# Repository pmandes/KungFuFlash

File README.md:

# Kung Fu Flash - Long PCB version

This version of the cartridge was developed for the following purposes:
- to fit into standard housings matching PCBs in format and size of the EasyFlash 3 cartridge
- to make SMD manual soldering easier
- to prevent the leverage effect when pressing the buttons from above, which stressed the cartridge connector and caused the C64 to crash.

The original design can be found [here](https://github.com/KimJorgensen/KungFuFlash).

Main changes:
- project migrated to KiCad 6.0
- 3D models for all components
- long PCB to fit common housings
- right angle tactile switches
- more durable Mini USB B socket for data transfer (you can use the same cable as EF3)
- 100Ω 0805 resistors for easier manual soldering (instead of resitor arrays)

The gerber files:
[KungFuFlash-Long-v2.1-PM.zip](https://github.com/pmandes/KungFuFlash/blob/long-board-cart/hardware/gerber/KungFuFlash-Long-v2.1-PM.zip)

Compatible housings:
- [KM-20B](https://www.tme.eu/en/details/km-20b/multipurpose-enclosures/maszczyk/)
- [Z7](https://www.kradex.eu/product/enclosures_two_part/z7_ps?lang=en)
- [Thingiverse](https://www.thingiverse.com/thing:1702546)
- "Commodore" type and others that EF3 fits

# Kung Fu Flash
Cartridge for the Commodore 64 that packs a punch.

Kung Fu Flash can emulate different cartridge types, load PRG files and use D64 disk images.
Just place your desired CRT, PRG or D64 files on a FAT formatted microSD card and use the built-in launcher to execute them.

## Hardware
There are three buttons on the cartridge; a reset button, a menu button for starting the launcher, and a special button that is used by the freezer cartridges.

The PCB will fit the Stumpy Cartridge Case from TFW8b, you just need to drill some holes for the buttons and make a cut for the microSD card.
If you have mounted the USB connector you will need to cut a hole for that as well.

You can also 3D print a cartridge case as the one designed by bigby, [see here](https://www.thingiverse.com/thing:4153414).

The gerber files and BOM can be found [here](https://github.com/KimJorgensen/KungFuFlash/releases/tag/rev.2).

## Supported Cartridges
The following cartridge types are currently supported:

* Normal cartridge (8k, 16k, Ultimax)
* Action Replay v4.x/v5/v6
* KCS Power Cartridge
* Final Cartridge III(+)
* Simons' BASIC
* Fun Play, Power Play
* Super Games
* Ocean type 1
* Epyx Fastload
* C64 Game System, System 3
* WarpSpeed
* Dinamic
* Zaxxon, Super Zaxxon
* Magic Desk, Domark, HES Australia
* Super Snapshot v5
* Comal-80
* EasyFlash
* Prophet64
* Freeze Frame
* Freeze Machine
* RGCD, Hucky
* Drean
* C128 Normal Cartridge (external function ROM)

## Supported File Types
The following file types are currently supported:

* Cartridge (CRT)
* C128 cartridge (ROM, BIN)
* Disk image (D64, D71, D81)
* Tape image (T64)
* Program (PRG, P00)
* Firmware update (UPD)

## USB Port
The USB port is active while the launcher is running allowing programs to be transferred from a PC using the EasyFlash 3 USB protocol.
Kung Fu Flash shows up as a standard serial port when connected to a PC not requiring any custom drivers to be installed.
This means, however, that the program on the PC side must be modified to support Kung Fu Flash.
For that reason a modified version of [EasyFlash 3 USB Utilities](3rd_party/ef3utils) and [EasyFlash 3 BBS](3rd_party/ef3bbs) has been included in this repository.

## Firmware Update
Just place the KungFuFlash_v1.xx.upd file on the SD card and select the file in the launcher to initiate the firmware update.
The newest firmware can be found [here](https://github.com/KimJorgensen/KungFuFlash/releases/).

For initial firmware installation, [see here](firmware/README.md).

## Limitations
Kung Fu Flash is a so called Software Defined Cartridge where a fast microcontroller emulates cartridge hardware in software.
This makes it extremely flexible, allowing different cartridge types to be supported at a relative low cost.

However, it can be challenging to get the C64 bus timing correct in software and in some places the timing is very close to the limit.
Even though Kung Fu Flash has been tested on different models of the Commodore 64, there is a chance that it doesn't work correctly on your specific model.
Use it at your own risk!

Kung Fu Flash will work with the PAL version of the Commodore 64 or Commodore 128. Support for the NTSC version is still considered experimental.

Disk drive emulation is using kernal vectors and will not work with fast loaders or software that uses direct hardware access which a lot of games does. Currently REL files are not supported and there is only limited write support.

## Thanks
Kung Fu Flash was based on or uses other open source projects:

* [EasyFlash 3](https://bitbucket.org/skoe/easyflash) by Thomas Giesel
* [Draco Browser](https://csdb.dk/release/?id=89910) by Sascha Bader
* [fatfs-stm32](https://github.com/colosimo/fatfs-stm32) by Aurelio Colosimo
* [FatFs](http://elm-chan.org/fsw/ff/00index_e.html) by ChaN
* [libusb_stm32](https://github.com/dmitrystu/libusb_stm32) by Dmitry Filimonchuk
* [stm32f4-bare-metal](https://github.com/fcayci/stm32f4-bare-metal) by Furkan Cayci
* [OpenC64Cart](https://github.com/SukkoPera/OpenC64Cart) by Giorgioggì
* [EasyFlash 3 USB Utilities](https://csdb.dk/release/?id=150097) by Tomaz Kac
* [Disk2easyflash](https://csdb.dk/release/?id=150323) by ALeX Kazik

and a few others. Please check the individual files for their license.

Thanks to Bjørn N. Jørgensen for giving this project its name.

Special thanks to the author of [Sidekick64](https://github.com/frntc/Sidekick64) Carsten Dachsbacher for his support and inspiration.

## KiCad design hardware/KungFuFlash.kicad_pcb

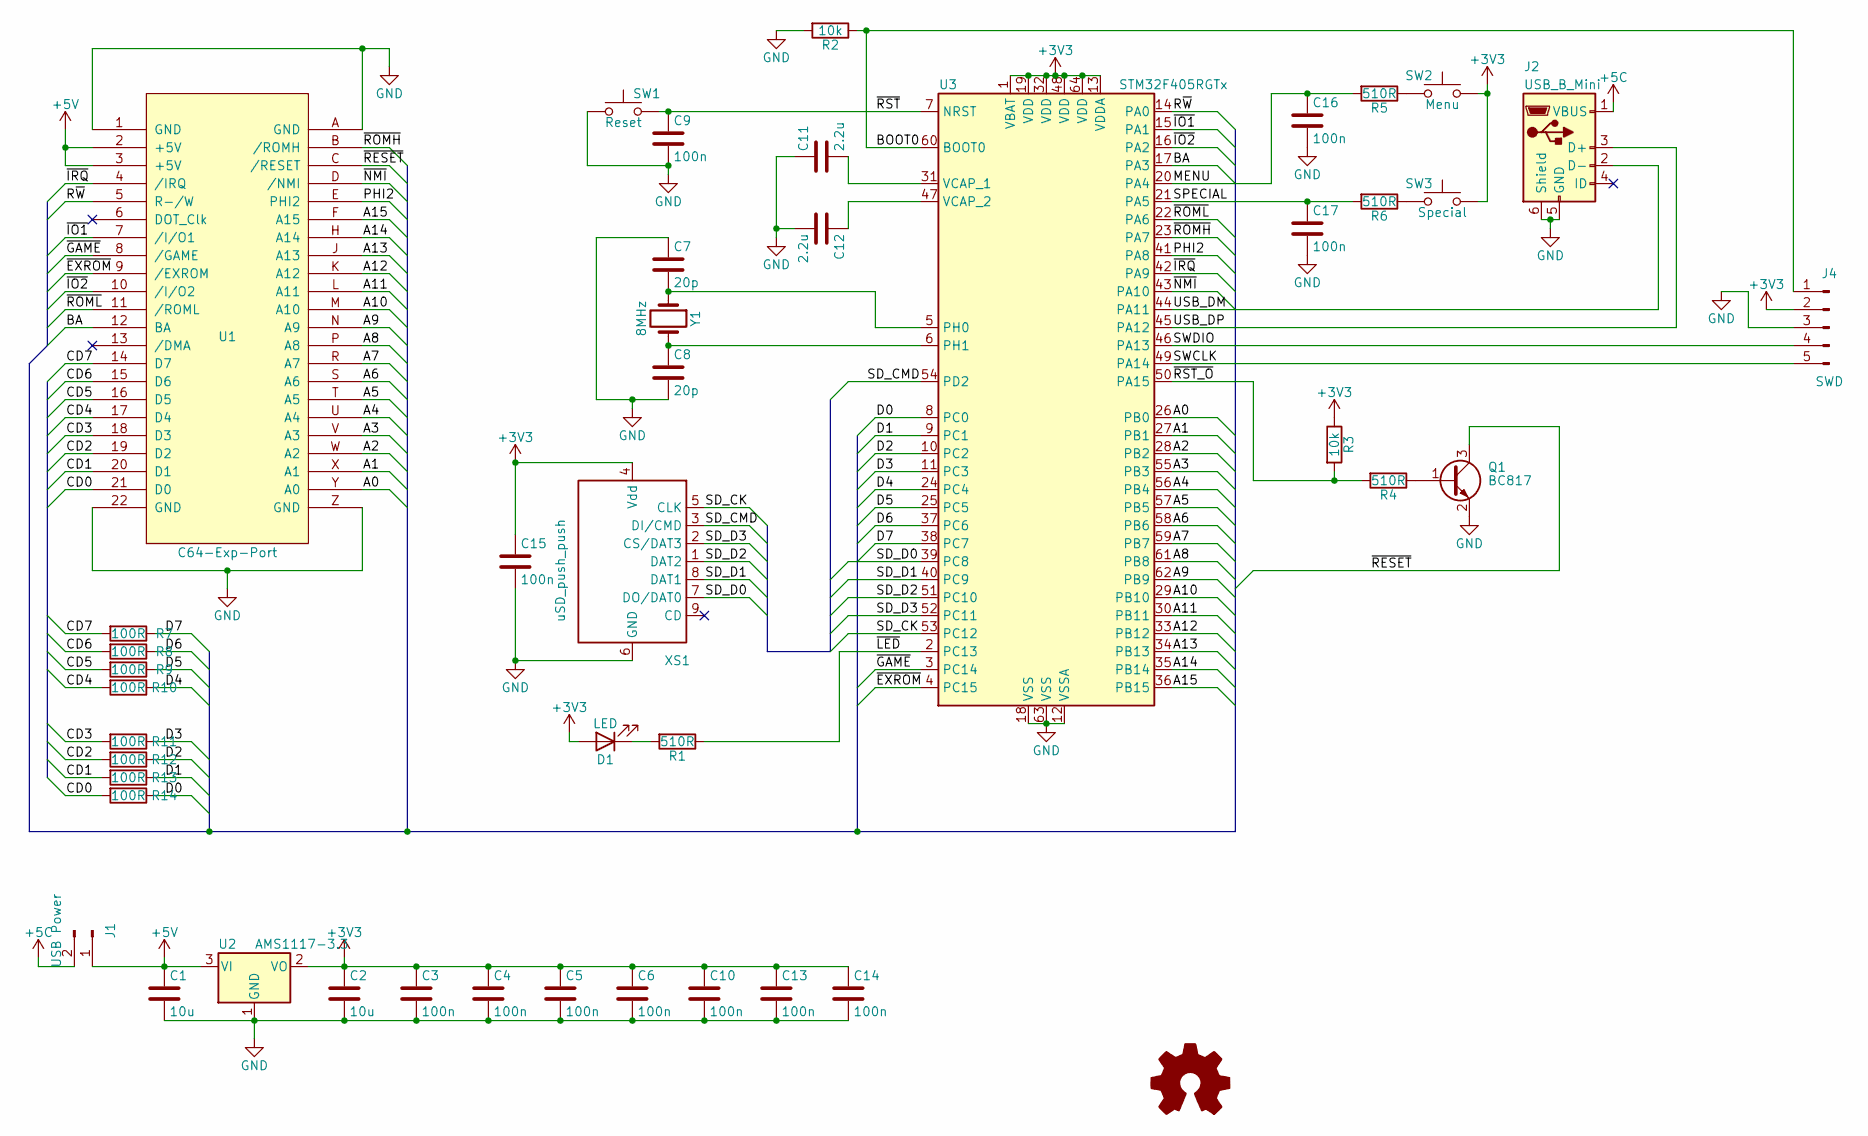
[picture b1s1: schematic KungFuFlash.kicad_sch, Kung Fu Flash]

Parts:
C1, C2: 10u; C_0805_2012Metric_Pad1.18x1.45mm_HandSolder
C3, C4, C5, C6, C9, C10, C13, C14, C15, C16: 100n; C_0603_1608Metric_Pad1.08x0.95mm_HandSolder
C7, C8: 20p; C_0603_1608Metric_Pad1.08x0.95mm_HandSolder
C11, C12: 2.2u; C_0805_2012Metric_Pad1.18x1.45mm_HandSolder
C17: 100n; C_0805_2012Metric_Pad1.18x1.45mm_HandSolder
D1: LED; LED_0805_2012Metric_Pad1.15x1.40mm_HandSolder
J1: USB Power; PinHeader_1x02_P2.54mm_Vertical
J2: USB_B_Mini; USB_Mini-B_Wuerth_65100516121_Horizontal
J4: SWD; PinHeader_1x05_P2.54mm_Vertical
Q1: BC817; SOT-23
R1, R4, R5, R6: 510R; R_0805_2012Metric_Pad1.20x1.40mm_HandSolder
R2, R3: 10k; R_0805_2012Metric_Pad1.20x1.40mm_HandSolder
R7, R8, R9, R10, R11, R12, R13, R14: 100R; R_0805_2012Metric_Pad1.20x1.40mm_HandSolder
SW1: Reset; SW_Tactile_SPST_Angled_PTS645Vx83-2LFS
SW2: Menu; SW_Tactile_SPST_Angled_PTS645Vx83-2LFS
SW3: Special; SW_Tactile_SPST_Angled_PTS645Vx83-2LFS
U1: C64-Exp-Port; C64-Cart
U2: AMS1117-3.3; SOT-223-3_TabPin2
U3: STM32F405RGTx; LQFP-64_10x10mm_P0.5mm
XS1: uSD_push_push; Conn_uSDcard
Y1: 8MHz; Crystal_SMD_5032-2Pin_5.0x3.2mm

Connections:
+3V3: C2.1, C3.1, C4.1, C5.1, C6.1, C10.1, C13.1, C14.1, C15.1, D1.2 (A), J4.2, R3.1, SW2.1, SW3.1, U2.2 (VO), U3.1 (VBAT), U3.13 (VDDA), U3.19 (VDD), U3.32 (VDD), U3.48 (VDD), U3.64 (VDD), XS1.4 (Vdd)
+5C: J1.2, J2.1 (VBUS)
+5V: C1.1, J1.1, U1.2 (+5V), U1.3 (+5V), U2.3 (VI)
/A0: U1.Y (A0), U3.26 (PB0)
/A1: U1.X (A1), U3.27 (PB1)
/A2: U1.W (A2), U3.28 (PB2)
/A3: U1.V (A3), U3.55 (PB3)
/A4: U1.U (A4), U3.56 (PB4)
/A5: U1.T (A5), U3.57 (PB5)
/A6: U1.S (A6), U3.58 (PB6)
/A7: U1.R (A7), U3.59 (PB7)
/A8: U1.P (A8), U3.61 (PB8)
/A9: U1.N (A9), U3.62 (PB9)
/A10: U1.M (A10), U3.29 (PB10)
/A11: U1.L (A11), U3.30 (PB11)
/A12: U1.K (A12), U3.33 (PB12)
/A13: U1.J (A13), U3.34 (PB13)
/A14: U1.H (A14), U3.35 (PB14)
/A15: U1.F (A15), U3.36 (PB15)
/BA: U1.12 (BA), U3.17 (PA3)
/BOOT0: J4.1, R2.1, U3.60 (BOOT0)
/CD0: R14.2, U1.21 (D0)
/CD1: R13.2, U1.20 (D1)
/CD2: R12.2, U1.19 (D2)
/CD3: R11.2, U1.18 (D3)
/CD4: R10.2, U1.17 (D4)
/CD5: R9.2, U1.16 (D5)
/CD6: R8.2, U1.15 (D6)
/CD7: R7.2, U1.14 (D7)
/D0: R14.1, U3.8 (PC0)
/D1: R13.1, U3.9 (PC1)
/D2: R12.1, U3.10 (PC2)
/D3: R11.1, U3.11 (PC3)
/D4: R10.1, U3.24 (PC4)
/D5: R9.1, U3.25 (PC5)
/D6: R8.1, U3.37 (PC6)
/D7: R7.1, U3.38 (PC7)
/MENU: C16.1, R5.2, U3.20 (PA4)
/PHI2: U1.E (PHI2), U3.41 (PA8)
/R~W: U1.5 (R-/W), U3.14 (PA0)
/SD_CK: U3.53 (PC12), XS1.5 (CLK)
/SD_CMD: U3.54 (PD2), XS1.3 (DI/CMD)
/SD_D0: U3.39 (PC8), XS1.7 (DO/DAT0)
/SD_D1: U3.40 (PC9), XS1.8 (DAT1)
/SD_D2: U3.51 (PC10), XS1.1 (DAT2)
/SD_D3: U3.52 (PC11), XS1.2 (CS/DAT3)
/SPECIAL: C17.1, R6.2, U3.21 (PA5)
/SWCLK: J4.5, U3.49 (PA14)
/SWDIO: J4.4, U3.46 (PA13)
/USB_DM: J2.2 (D-), U3.44 (PA11)
/USB_DP: J2.3 (D+), U3.45 (PA12)
/~EXROM: U1.9 (/EXROM), U3.4 (PC15)
/~GAME: U1.8 (/GAME), U3.3 (PC14)
/~IO1: U1.7 (/I/O1), U3.15 (PA1)
/~IO2: U1.10 (/I/O2), U3.16 (PA2)
/~IRQ: U1.4 (/IRQ), U3.42 (PA9)
/~LED: R1.1, U3.2 (PC13)
/~NMI: U1.D (/NMI), U3.43 (PA10)
/~RESET: Q1.3 (C), U1.C (/RESET)
/~ROMH: U1.B (/ROMH), U3.23 (PA7)
/~ROML: U1.11 (/ROML), U3.22 (PA6)
/~RST_O: R3.2, R4.2, U3.50 (PA15)
/~RST: C9.1, SW1.2, U3.7 (NRST)
GND: C1.2, C2.2, C3.2, C4.2, C5.2, C6.2, C7.1, C8.2, C9.2, C10.2, C11.1, C12.2, C13.2, C14.2, C15.2, C16.2, C17.2, J2.5 (GND), J2.6 (Shield), J4.3, Q1.2 (E), R2.2, SW1.1, U1.1 (GND), U1.22 (GND), U1.A (GND), U1.Z (GND), U2.1 (GND), U3.12 (VSSA), U3.18 (VSS), U3.63 (VSS), XS1.6 (GND)
unnamed: C7.2, U3.5 (PH0), Y1.1
unnamed: C8.1, U3.6 (PH1), Y1.2
unnamed: C11.2, U3.31 (VCAP_1)
unnamed: C12.1, U3.47 (VCAP_2)
unnamed: D1.1 (K), R1.2
unnamed: Q1.1 (B), R4.1
unnamed: R5.1, SW2.2
unnamed: R6.1, SW3.2

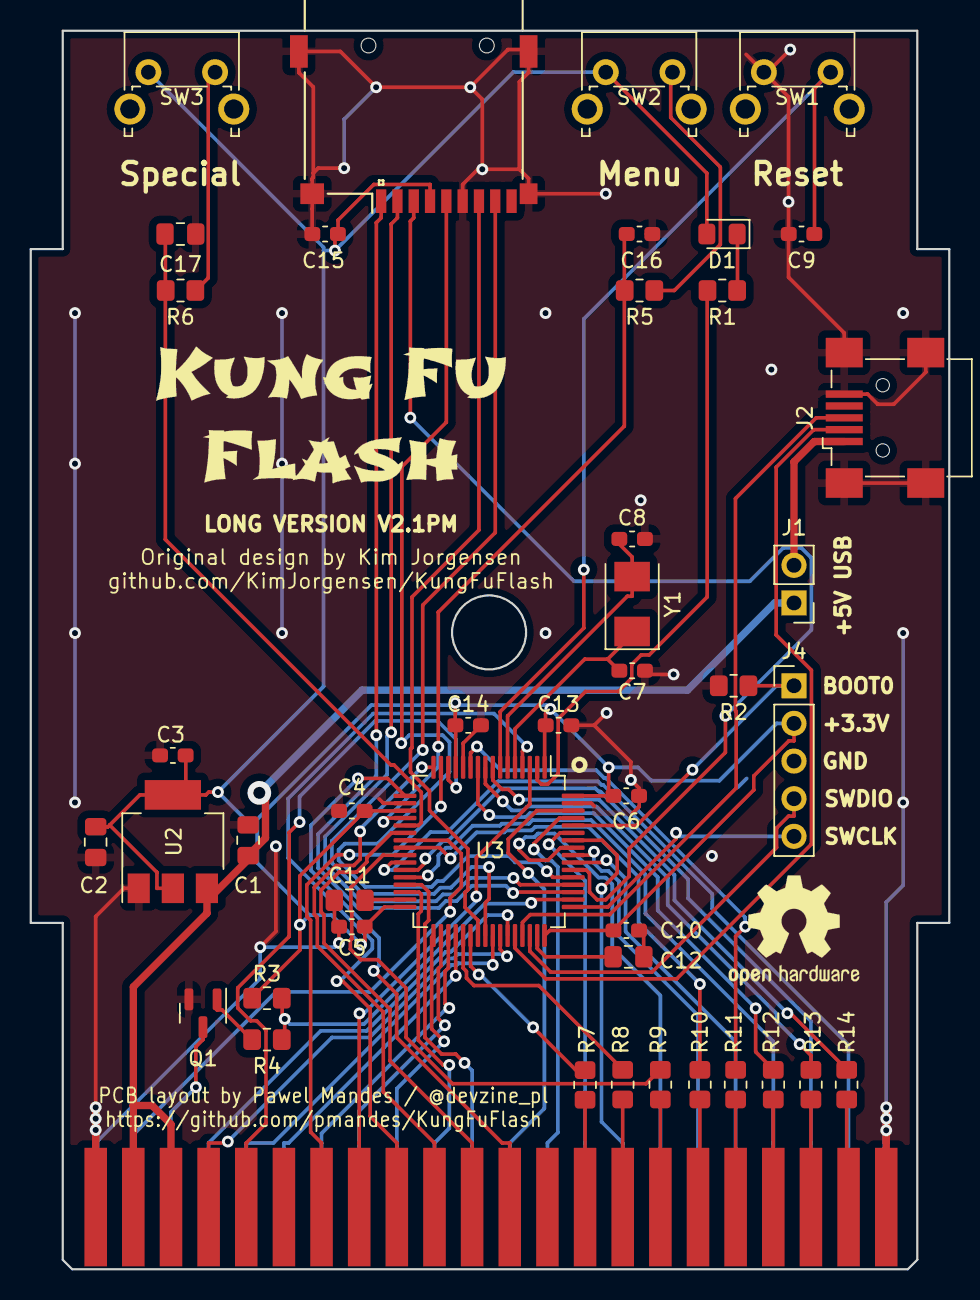
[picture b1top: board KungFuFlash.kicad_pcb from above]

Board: 2 copper layers, 62.0 x 83.6 mm, 44 parts (0 on the bottom side), 72 nets.

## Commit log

2021-03-18 Long board cart PCB layout.
2021-03-19 Trace routing and layout cleanup.
2021-03-20 New pics of the long PCB version.
2021-03-24 Tracks / vias optimization.
2021-03-25 GND layers adjustments.
2021-04-25 3D model and layers cleanup
2022-01-11 Project migrated to KiCad 6.0
